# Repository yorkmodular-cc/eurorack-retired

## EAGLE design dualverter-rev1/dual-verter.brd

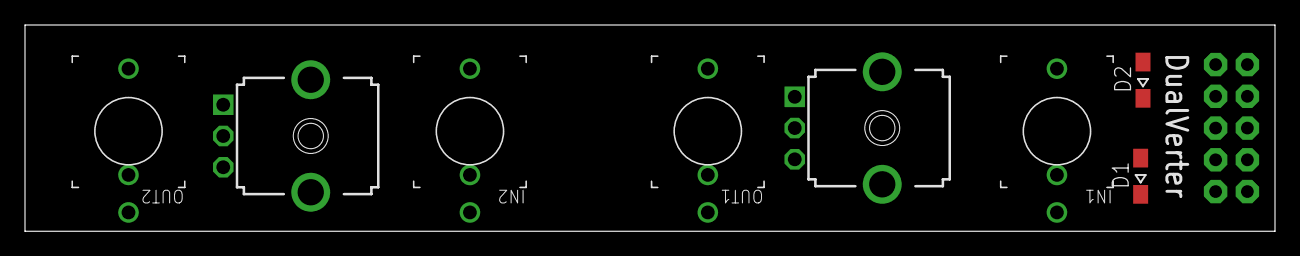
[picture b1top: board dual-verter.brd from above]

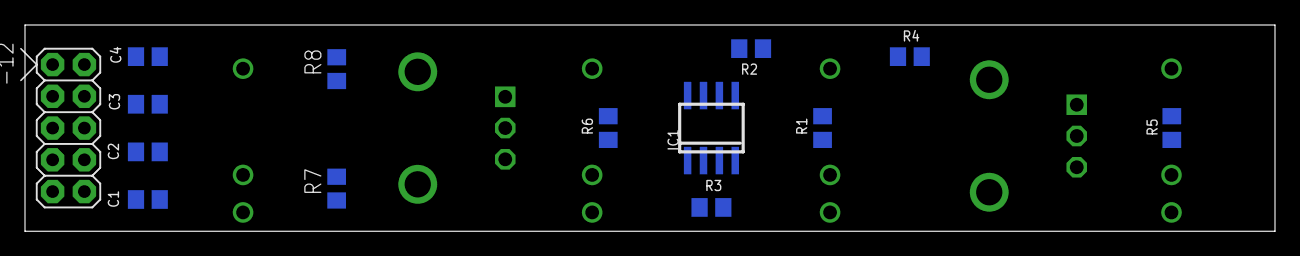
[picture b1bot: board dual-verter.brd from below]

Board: 2 copper layers, 100.0 x 16.5 mm, 22 parts (14 on the bottom side), 15 nets, no tracks yet.

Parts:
C1, C4: 10u; C0805
C2, C3: 0.1u; C0805
D1, D2: BAT54; SOD323-W
IC1: TL072D; SO08
IN1, IN2: THONKICONNNEW; WQP-PJ301M-12_JACK
OUT1, OUT2: THONKICONNNEW; WQP-PJ301M-12_JACK
POWER1: POWER_SIMPLE10; POWER_10
R1, R2, R3, R4, R5, R6: 200k; R0805
R7, R8: FERRITE; R0805
VR1, VR2: 100k; 9MM_SNAP-IN_POT

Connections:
+12V: C1.1, C2.1, D1.C, IC1.8, R7.2
-12V: C3.2, C4.2, D2.A, IC1.4, R8.1
GND: C1.2, C2.2, C3.1, C4.1, D1.A, D2.C, IN1.P$2_SWITCH, IN1.P$3_SLEEVE, IN2.P$3_SLEEVE, OUT1.P$2_SWITCH, OUT1.P$3_SLEEVE, OUT2.P$2_SWITCH, OUT2.P$3_SLEEVE, POWER1.3, POWER1.4, POWER1.5, POWER1.6, POWER1.7, POWER1.8, VR1.1, VR2.1
IN1: IN1.P$1_TIP, IN2.P$2_SWITCH, R1.1, VR1.3
unnamed: IC1.3, VR1.2
unnamed: IC1.5, VR2.2
unnamed: IC1.7, R4.2, R5.1
unnamed: IN2.P$1_TIP, R2.1, VR2.3
unnamed: IC1.1, R3.2, R6.1
unnamed: IC1.2, R1.2, R3.1
unnamed: POWER1.9, POWER1.10, R7.1
unnamed: IC1.6, R2.2, R4.1
unnamed: OUT2.P$1_TIP, R5.2
unnamed: OUT1.P$1_TIP, R6.2
unnamed: POWER1.1, POWER1.2, R8.2

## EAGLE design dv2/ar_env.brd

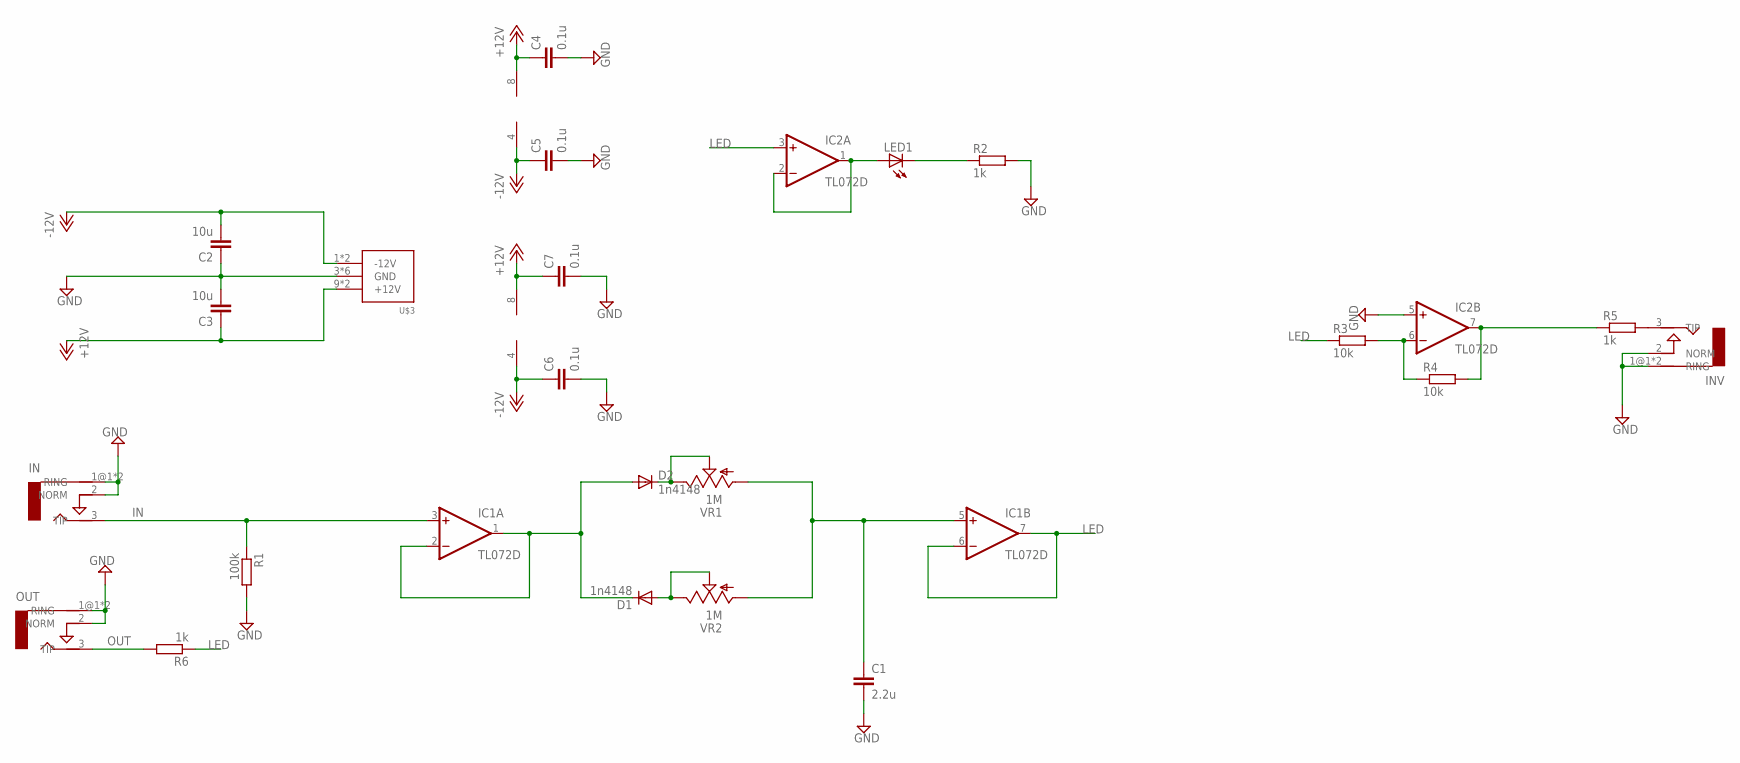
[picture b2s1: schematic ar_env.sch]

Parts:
C1: 2.2u; C0805
C2, C3: 10u; C0805
C4, C5, C6, C7: 0.1u; C0805
D1, D2: 1n4148; SOD323-W
IC1, IC2: TL072D; SO08
IN: AUDIO-JACKERTHENVAR; ERTHENVAR-JACK
INV: AUDIO-JACKERTHENVAR; ERTHENVAR-JACK
LED1: LEDCHIP-LED0805; CHIP-LED0805
OUT: AUDIO-JACKERTHENVAR; ERTHENVAR-JACK
R1: 100k; R0805
R2, R5, R6: 1k; R0805
R3, R4: 10k; R0805
U$3: POWER_SIMPLE10; POWER_10
VR1, VR2: 1M; 9MM_SNAP-IN_POT

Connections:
+12V: C3.1, C4.1, C7.1, IC1.8 (V+), IC2.8 (V+), U$3.9 (+12V), U$3.10 (+12V)
-12V: C2.2, C5.1, C6.1, IC1.4 (V-), IC2.4 (V-), U$3.1 (-12V), U$3.2 (-12V)
GND: C1.2, C2.1, C3.2, C4.2, C5.2, C6.2, C7.2, IC2.5 (+IN), IN.1@1 (RING), IN.1@2 (RING), IN.2 (NORM), INV.1@1 (RING), INV.1@2 (RING), INV.2 (NORM), OUT.1@1 (RING), OUT.1@2 (RING), OUT.2 (NORM), R1.2, R2.2, U$3.3 (GND), U$3.4 (GND), U$3.5 (GND), U$3.6 (GND), U$3.7 (GND), U$3.8 (GND)
IN: IC1.3 (+IN), IN.3 (TIP), R1.1
LED: IC1.6 (-IN), IC1.7 (OUT), IC2.3 (+IN), R3.1, R6.1
unnamed: D2.C, VR1.2 (S), VR1.3 (E)
unnamed: D1.A, VR2.2 (S), VR2.3 (E)
unnamed: D1.C, D2.A, IC1.1 (OUT), IC1.2 (-IN)
unnamed: IC2.1 (OUT), IC2.2 (-IN), LED1.A
unnamed: C1.1, IC1.5 (+IN), VR1.1 (A), VR2.1 (A)
unnamed: IC2.7 (OUT), R4.2, R5.1
unnamed: IC2.6 (-IN), R3.2, R4.1
unnamed: LED1.C, R2.1
unnamed: INV.3 (TIP), R5.2
OUT: OUT.3 (TIP), R6.2

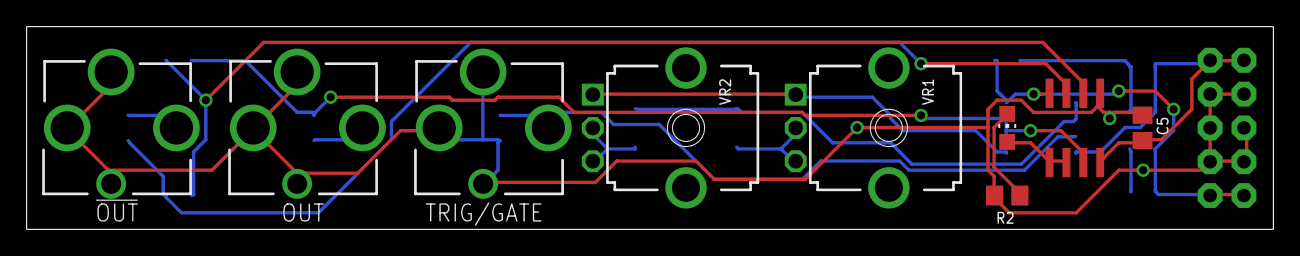
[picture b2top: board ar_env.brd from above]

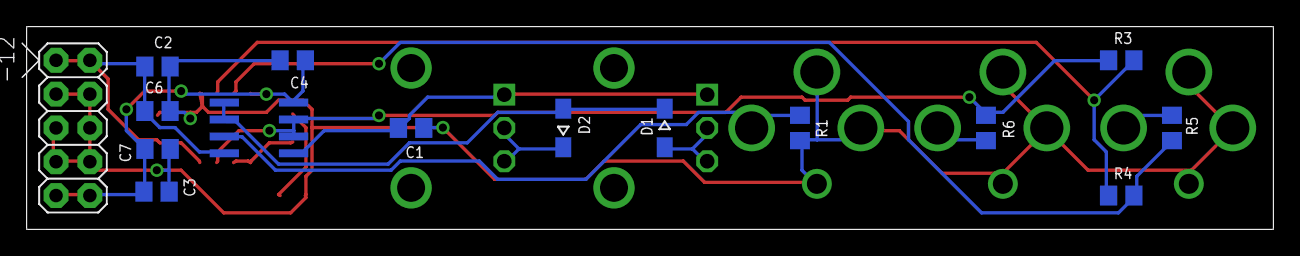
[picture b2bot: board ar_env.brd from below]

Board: 2 copper layers, 93.6 x 15.2 mm, 24 parts (15 on the bottom side), 15 nets.

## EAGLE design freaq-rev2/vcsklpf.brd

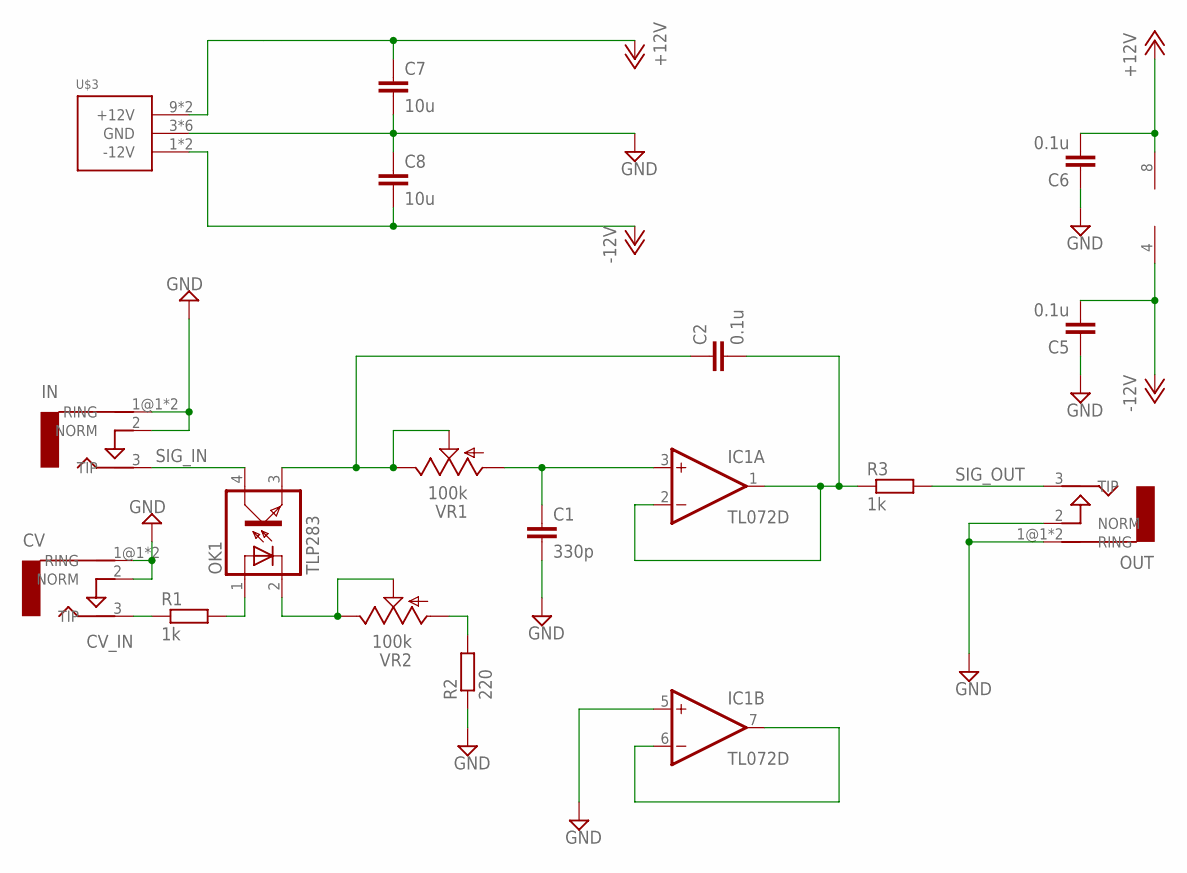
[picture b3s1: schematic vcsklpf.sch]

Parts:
C1: 330p; C0805
C2, C5, C6: 0.1u; C0805
C7, C8: 10u; C0805
CV: AUDIO-JACKERTHENVAR; ERTHENVAR-JACK
IC1: TL072D; SO08
IN: AUDIO-JACKERTHENVAR; ERTHENVAR-JACK
OK1: TLP283; MINI-FLAT-4
OUT: AUDIO-JACKERTHENVAR; ERTHENVAR-JACK
R1, R3: 1k; R0805
R2: 220; R0805
U$3: POWER_SIMPLE10; POWER_10
VR1, VR2: 100k; 9MM_SNAP-IN_POT

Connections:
+12V: C6.2, C7.1, IC1.8 (V+), U$3.9 (+12V), U$3.10 (+12V)
-12V: C5.2, C8.2, IC1.4 (V-), U$3.1 (-12V), U$3.2 (-12V)
CV_IN: CV.3 (TIP), R1.1
GND: C1.2, C5.1, C6.1, C7.2, C8.1, CV.1@1 (RING), CV.1@2 (RING), CV.2 (NORM), IC1.5 (+IN), IN.1@1 (RING), IN.1@2 (RING), IN.2 (NORM), OUT.1@1 (RING), OUT.1@2 (RING), OUT.2 (NORM), R2.1, U$3.3 (GND), U$3.4 (GND), U$3.5 (GND), U$3.6 (GND), U$3.7 (GND), U$3.8 (GND)
unnamed: C2.2, IC1.1 (OUT), IC1.2 (-IN), R3.1
unnamed: C1.1, IC1.3 (+IN), VR1.1 (A)
unnamed: C2.1, OK1.3 (EMIT), VR1.2 (S), VR1.3 (E)
unnamed: IC1.6 (-IN), IC1.7 (OUT)
unnamed: OK1.2 (C), VR2.2 (S), VR2.3 (E)
unnamed: OK1.1 (A), R1.2
unnamed: R2.2, VR2.1 (A)
SIG_IN: IN.3 (TIP), OK1.4 (COL)
SIG_OUT: OUT.3 (TIP), R3.2

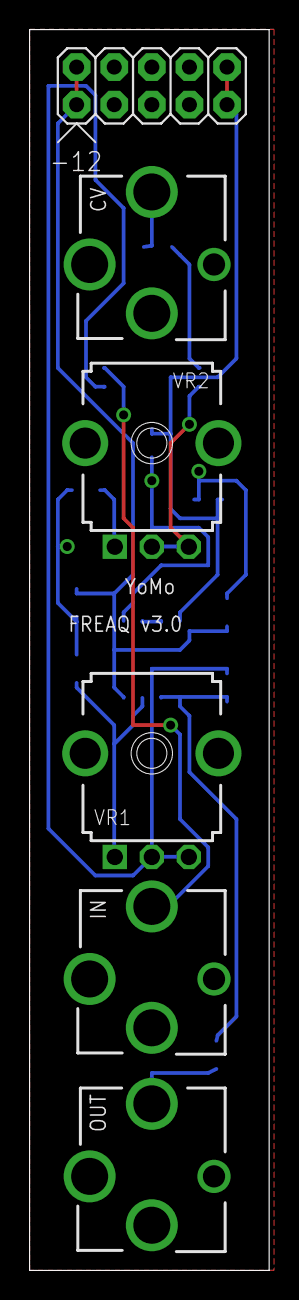
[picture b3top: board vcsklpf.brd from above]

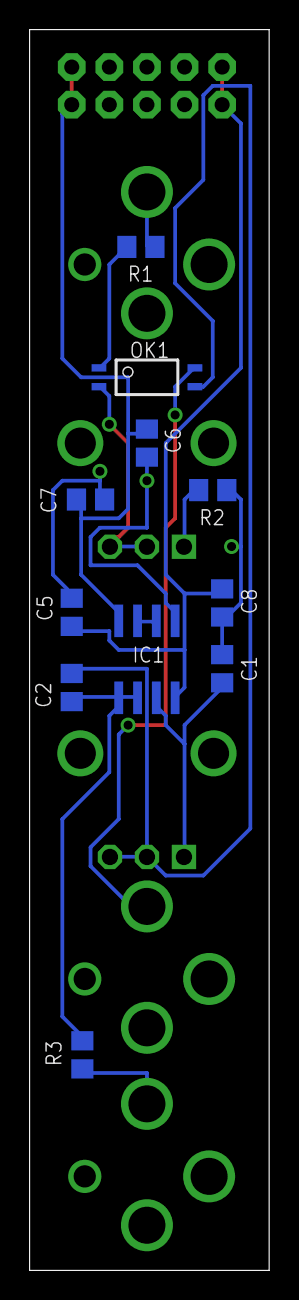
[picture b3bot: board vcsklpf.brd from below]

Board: 2 copper layers, 16.2 x 83.8 mm, 17 parts (11 on the bottom side), 13 nets.

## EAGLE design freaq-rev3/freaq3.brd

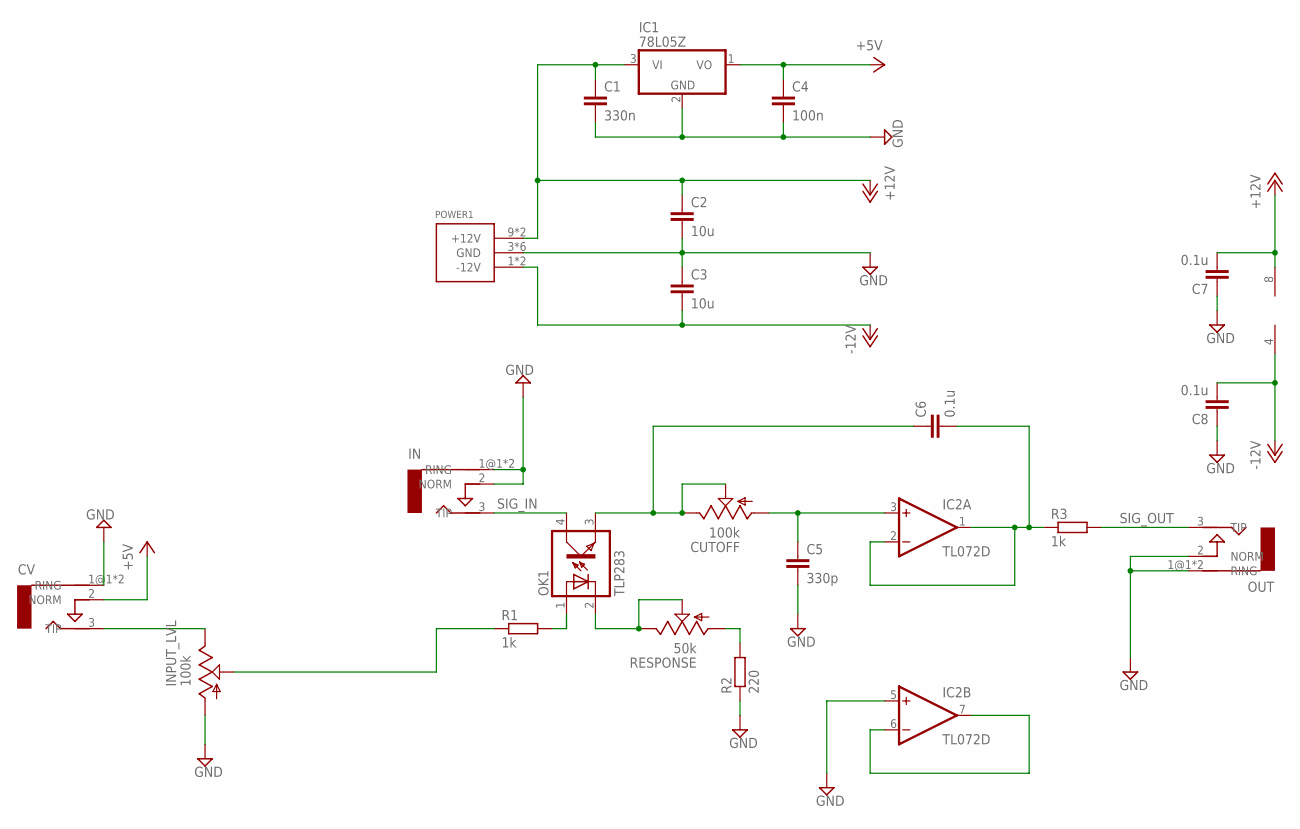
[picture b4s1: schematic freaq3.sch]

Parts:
C1: 330n; C0805
C2, C3: 10u; C0805
C4: 100n; C0805
C5: 330p; C0805
C6, C7, C8: 0.1u; C0805
CUTOFF: 100k; 9MM_SNAP-IN_POT
CV: AUDIO-JACKERTHENVAR; ERTHENVAR-JACK
IC1: 78L05Z; TO92
IC2: TL072D; SO08
IN: AUDIO-JACKERTHENVAR; ERTHENVAR-JACK
INPUT_LVL: 100k; 9MM_SNAP-IN_POT
OK1: TLP283; MINI-FLAT-4
OUT: AUDIO-JACKERTHENVAR; ERTHENVAR-JACK
POWER1: POWER_SIMPLE10; POWER_10
R1, R3: 1k; R0805
R2: 220; R0805
RESPONSE: 50k; 9MM_SNAP-IN_POT

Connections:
+5V: C4.1, CV.2 (NORM), IC1.1 (VO)
+12V: C1.1, C2.1, C7.2, IC1.3 (VI), IC2.8 (V+), POWER1.9 (+12V), POWER1.10 (+12V)
-12V: C3.2, C8.2, IC2.4 (V-), POWER1.1 (-12V), POWER1.2 (-12V)
GND: C1.2, C2.2, C3.1, C4.2, C5.2, C7.1, C8.1, CV.1@1 (RING), CV.1@2 (RING), IC1.2 (GND), IC2.5 (+IN), IN.1@1 (RING), IN.1@2 (RING), IN.2 (NORM), INPUT_LVL.1 (A), OUT.1@1 (RING), OUT.1@2 (RING), OUT.2 (NORM), POWER1.3 (GND), POWER1.4 (GND), POWER1.5 (GND), POWER1.6 (GND), POWER1.7 (GND), POWER1.8 (GND), R2.1
unnamed: C6.2, IC2.1 (OUT), IC2.2 (-IN), R3.1
unnamed: C5.1, CUTOFF.1 (A), IC2.3 (+IN)
unnamed: C6.1, CUTOFF.2 (S), CUTOFF.3 (E), OK1.3 (EMIT)
unnamed: INPUT_LVL.2 (S), R1.1
unnamed: IC2.6 (-IN), IC2.7 (OUT)
unnamed: CV.3 (TIP), INPUT_LVL.3 (E)
unnamed: OK1.2 (C), RESPONSE.2 (S), RESPONSE.3 (E)
unnamed: OK1.1 (A), R1.2
unnamed: R2.2, RESPONSE.1 (A)
SIG_IN: IN.3 (TIP), OK1.4 (COL)
SIG_OUT: OUT.3 (TIP), R3.2

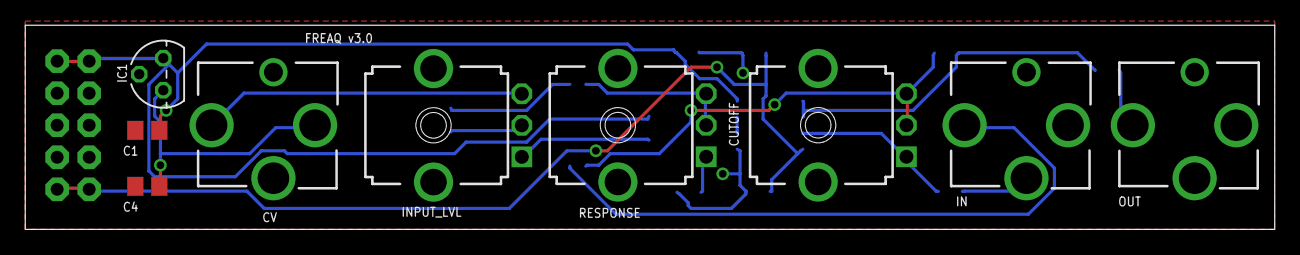
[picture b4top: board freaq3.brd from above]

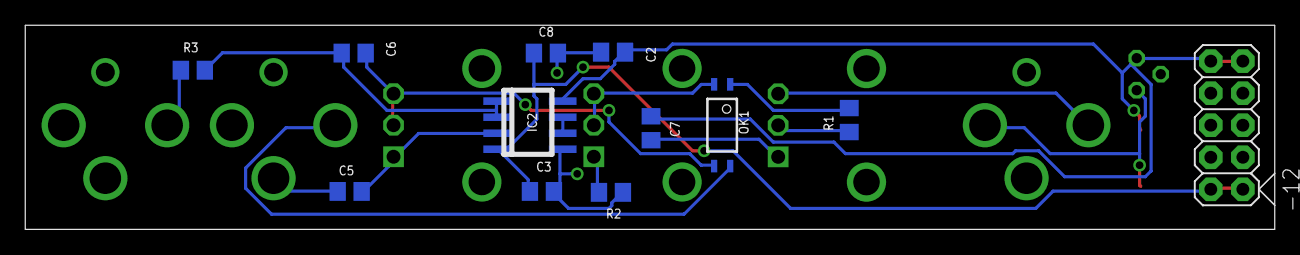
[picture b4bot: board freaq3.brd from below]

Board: 2 copper layers, 99.1 x 16.2 mm, 21 parts (12 on the bottom side), 15 nets.

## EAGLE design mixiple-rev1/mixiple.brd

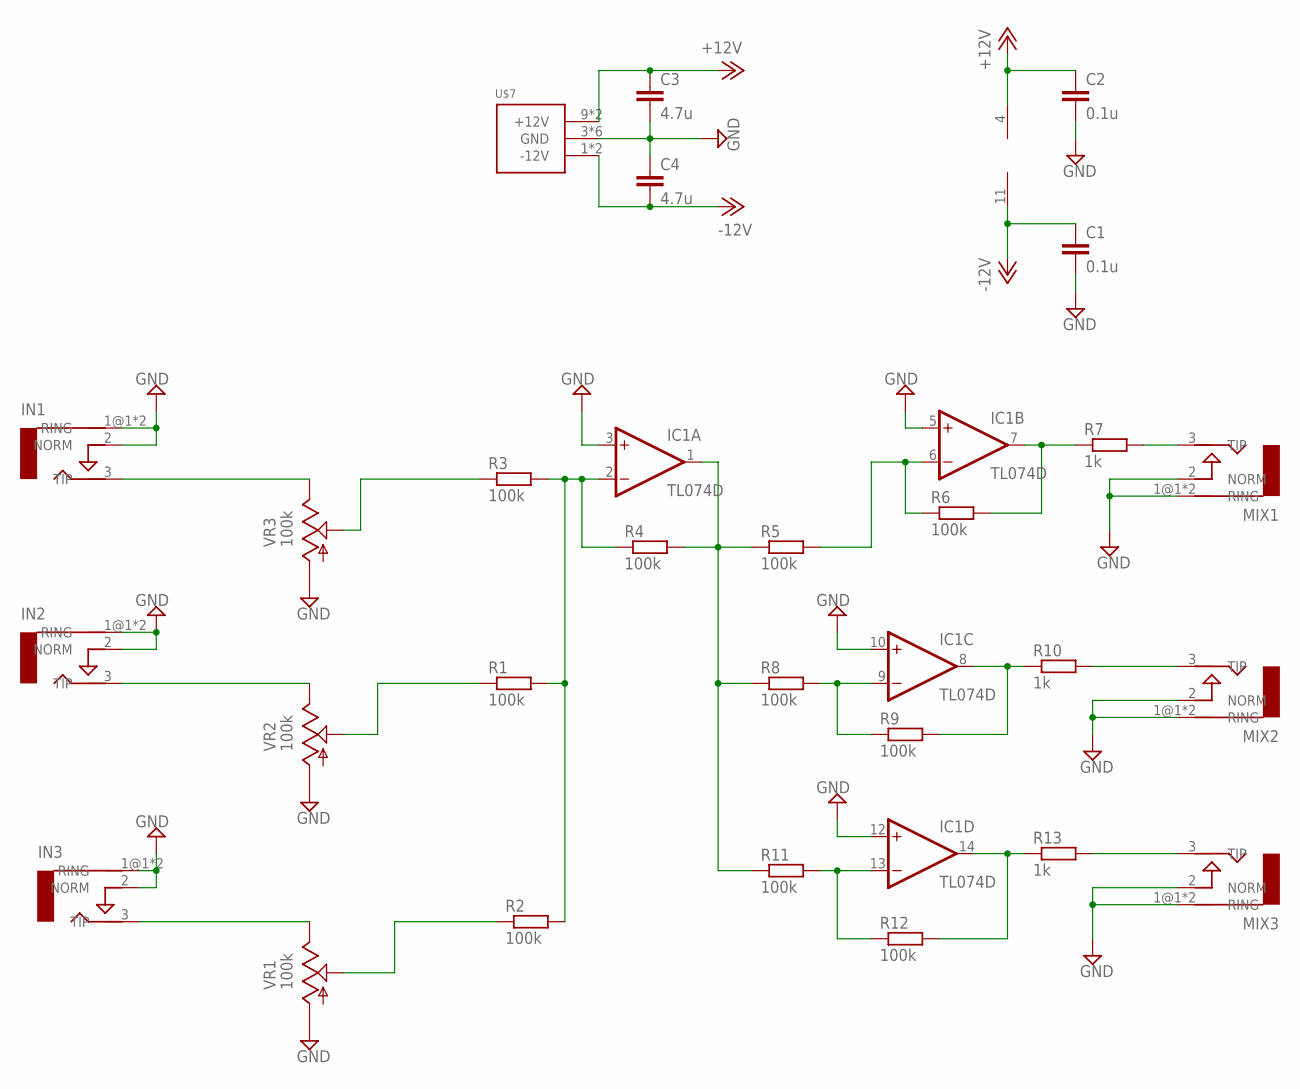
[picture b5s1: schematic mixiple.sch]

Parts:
C1, C2: 0.1u; C0805
C3, C4: 4.7u; C0805
IC1: TL074D; SO14
IN1, IN2, IN3: AUDIO-JACKERTHENVAR; ERTHENVAR-JACK
MIX1, MIX2, MIX3: AUDIO-JACKERTHENVAR; ERTHENVAR-JACK
R1, R2, R3, R4, R5, R6, R8, R9, R11, R12: 100k; R0805
R7, R10, R13: 1k; R0805
U$7: POWER_SIMPLE10; POWER_10
VR1, VR2, VR3: 100k; 9MM_SNAP-IN_POT

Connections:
+12V: C2.1, C3.1, IC1.4 (V+), U$7.9 (+12V), U$7.10 (+12V)
-12V: C1.1, C4.2, IC1.11 (V-), U$7.1 (-12V), U$7.2 (-12V)
GND: C1.2, C2.2, C3.2, C4.1, IC1.3 (+IN), IC1.5 (+IN), IC1.10 (+IN), IC1.12 (+IN), IN1.1@1 (RING), IN1.1@2 (RING), IN1.2 (NORM), IN2.1@1 (RING), IN2.1@2 (RING), IN2.2 (NORM), IN3.1@1 (RING), IN3.1@2 (RING), IN3.2 (NORM), MIX1.1@1 (RING), MIX1.1@2 (RING), MIX1.2 (NORM), MIX2.1@1 (RING), MIX2.1@2 (RING), MIX2.2 (NORM), MIX3.1@1 (RING), MIX3.1@2 (RING), MIX3.2 (NORM), U$7.3 (GND), U$7.4 (GND), U$7.5 (GND), U$7.6 (GND), U$7.7 (GND), U$7.8 (GND), VR1.1 (A), VR2.1 (A), VR3.1 (A)
unnamed: R2.1, VR1.2 (S)
unnamed: R1.1, VR2.2 (S)
unnamed: R3.1, VR3.2 (S)
unnamed: IC1.7 (OUT), R6.2, R7.1
unnamed: IC1.8 (OUT), R9.2, R10.1
unnamed: IC1.14 (OUT), R12.2, R13.1
unnamed: IC1.6 (-IN), R5.2, R6.1
unnamed: IC1.9 (-IN), R8.2, R9.1
unnamed: IC1.13 (-IN), R11.2, R12.1
unnamed: IN1.3 (TIP), VR3.3 (E)
unnamed: IC1.2 (-IN), R1.2, R2.2, R3.2, R4.1
unnamed: IN2.3 (TIP), VR2.3 (E)
unnamed: IN3.3 (TIP), VR1.3 (E)
unnamed: IC1.1 (OUT), R4.2, R5.1, R8.1, R11.1
unnamed: MIX2.3 (TIP), R10.2
unnamed: MIX3.3 (TIP), R13.2
unnamed: MIX1.3 (TIP), R7.2

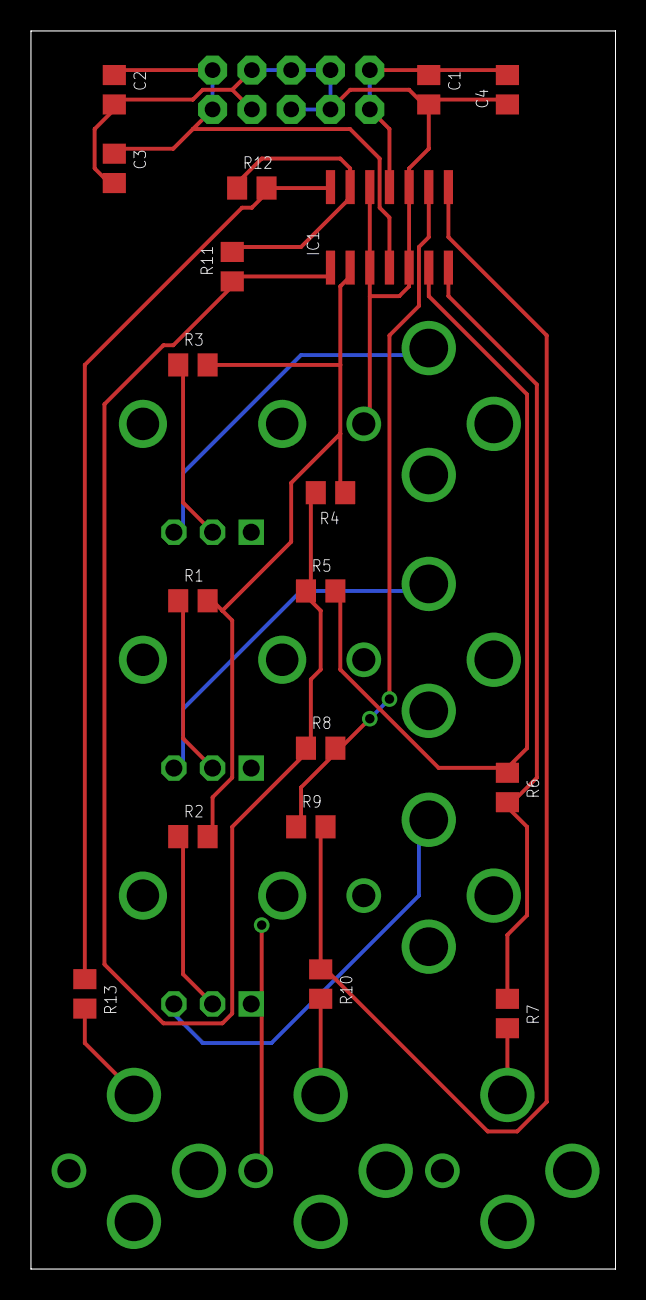
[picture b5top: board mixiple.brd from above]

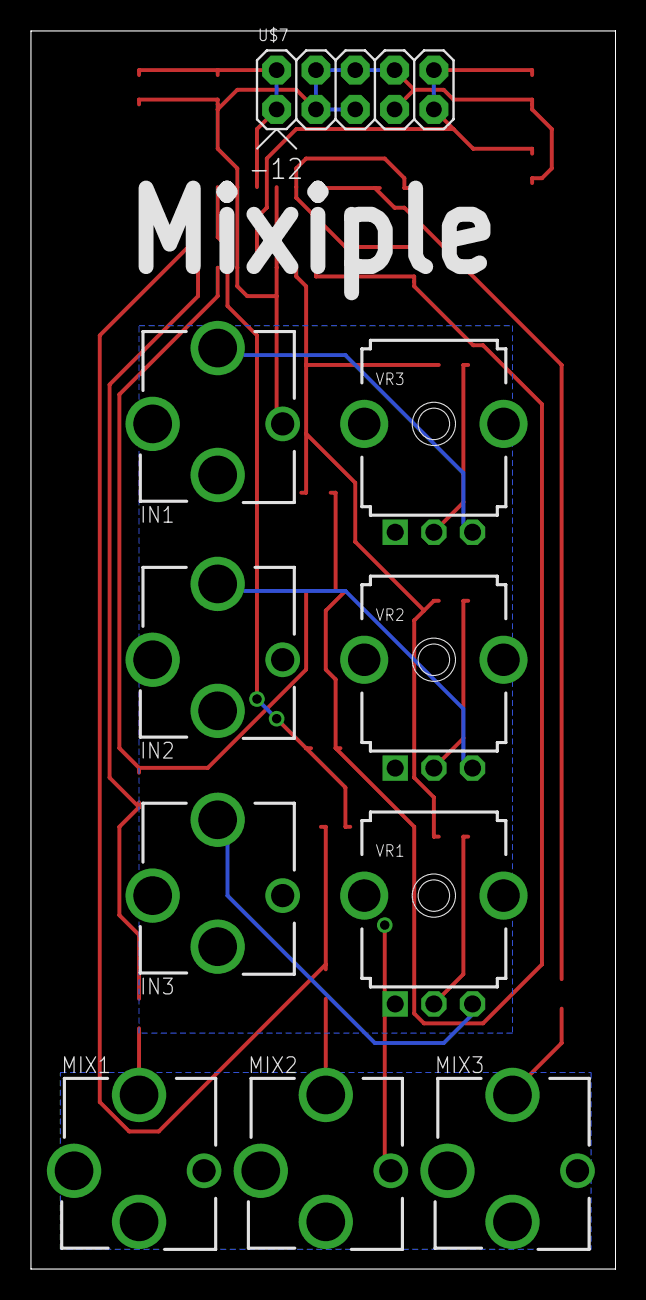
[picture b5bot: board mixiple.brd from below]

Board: 2 copper layers, 37.8 x 80.0 mm, 28 parts (10 on the bottom side), 20 nets.

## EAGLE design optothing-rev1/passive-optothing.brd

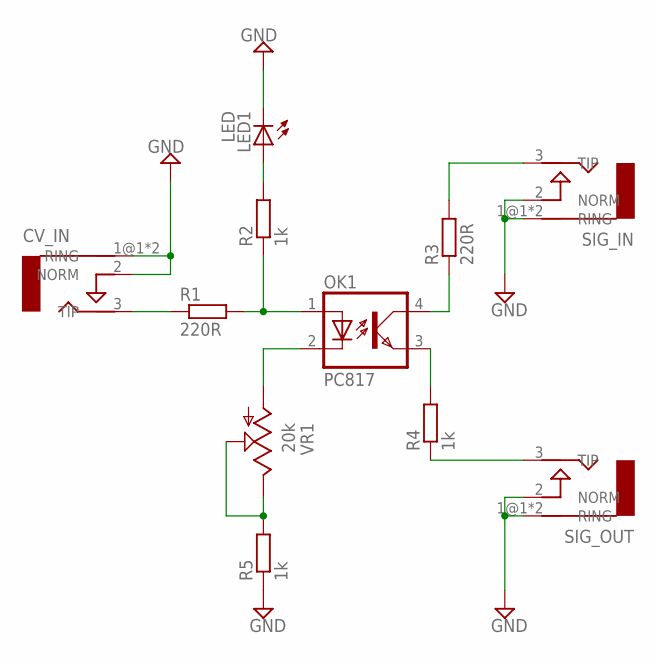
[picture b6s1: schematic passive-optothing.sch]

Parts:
CV_IN: AUDIO-JACKERTHENVAR; ERTHENVAR-JACK
LED1: LED; LED3MM
OK1: PC817; DIL04
R1, R3: 220R; R0805
R2, R4, R5: 1k; R0805
SIG_IN: AUDIO-JACKERTHENVAR; ERTHENVAR-JACK
SIG_OUT: AUDIO-JACKERTHENVAR; ERTHENVAR-JACK
VR1: 20k; 9MM_SNAP-IN_POT

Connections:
CV_IN: OK1.1 (A), R1.2, R2.1
CV_OUT: OK1.2 (C), VR1.1 (A)
GND: CV_IN.1@1 (RING), CV_IN.1@2 (RING), CV_IN.2 (NORM), LED1.K (C), R5.1, SIG_IN.1@1 (RING), SIG_IN.1@2 (RING), SIG_IN.2 (NORM), SIG_OUT.1@1 (RING), SIG_OUT.1@2 (RING), SIG_OUT.2 (NORM)
unnamed: R5.2, VR1.2 (S), VR1.3 (E)
unnamed: R4.1, SIG_OUT.3 (TIP)
unnamed: OK1.4 (COL), R3.1
unnamed: CV_IN.3 (TIP), R1.1
unnamed: LED1.A, R2.2
SIG_IN: R3.2, SIG_IN.3 (TIP)
SIG_OUT: OK1.3 (EMIT), R4.2

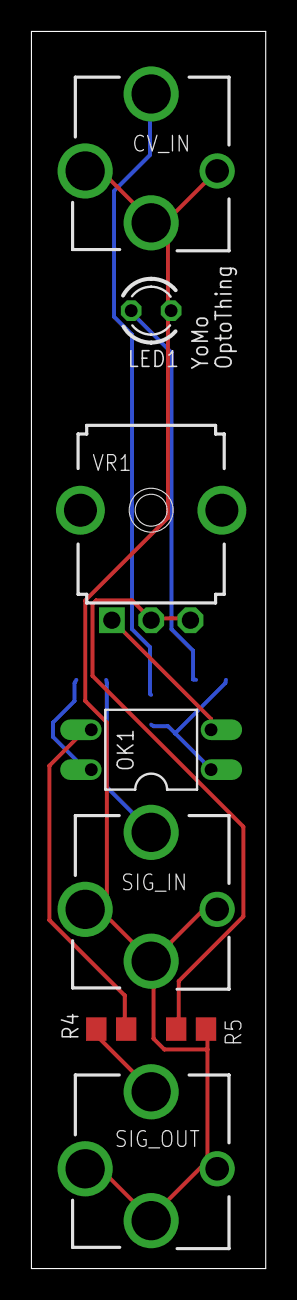
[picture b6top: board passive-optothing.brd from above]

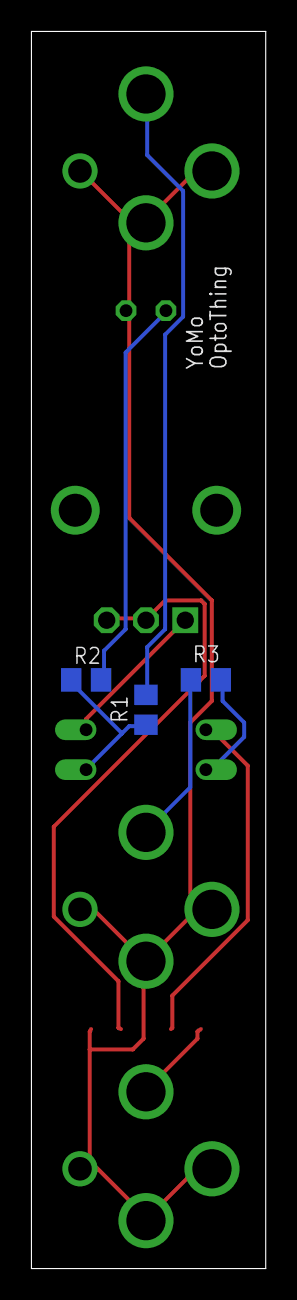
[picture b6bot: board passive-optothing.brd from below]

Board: 2 copper layers, 14.9 x 78.7 mm, 11 parts (3 on the bottom side), 10 nets.

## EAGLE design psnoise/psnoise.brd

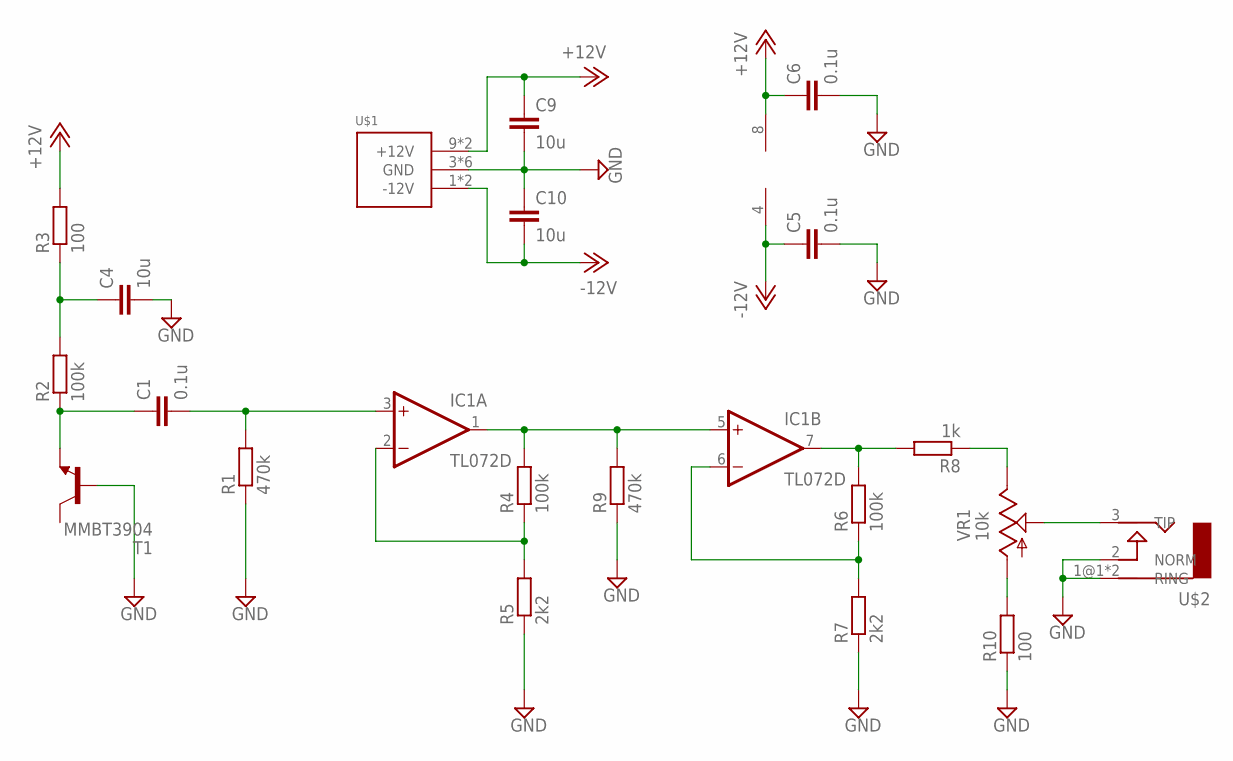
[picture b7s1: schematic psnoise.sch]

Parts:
C1, C5, C6: 0.1u; C0805
C4, C9, C10: 10u; C0805
IC1: TL072D; SO08
R1, R9: 470k; R0805
R2, R4, R6: 100k; R0805
R3, R10: 100; R0805
R5, R7: 2k2; R0805
R8: 1k; R0805
T1: MMBT3904; SOT23-BEC
U$1: POWER_SIMPLE10; POWER_10
U$2: AUDIO-JACKERTHENVAR; ERTHENVAR-JACK
VR1: 10k; 9MM_SNAP-IN_POT

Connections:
+12V: C6.1, C9.1, IC1.8 (V+), R3.2, U$1.9 (+12V), U$1.10 (+12V)
-12V: C5.1, C10.2, IC1.4 (V-), U$1.1 (-12V), U$1.2 (-12V)
GND: C4.2, C5.2, C6.2, C9.2, C10.1, R1.1, R5.1, R7.1, R9.1, R10.1, T1.B, U$1.3 (GND), U$1.4 (GND), U$1.5 (GND), U$1.6 (GND), U$1.7 (GND), U$1.8 (GND), U$2.1@1 (RING), U$2.1@2 (RING), U$2.2 (NORM)
unnamed: IC1.2 (-IN), R4.1, R5.2
unnamed: IC1.1 (OUT), IC1.5 (+IN), R4.2, R9.2
unnamed: R10.2, VR1.1 (A)
unnamed: IC1.6 (-IN), R6.1, R7.2
unnamed: IC1.7 (OUT), R6.2, R8.2
unnamed: R8.1, VR1.3 (E)
unnamed: C1.2, IC1.3 (+IN), R1.2
unnamed: U$2.3 (TIP), VR1.2 (S)
unnamed: C4.1, R2.2, R3.1
unnamed: C1.1, R2.1, T1.E

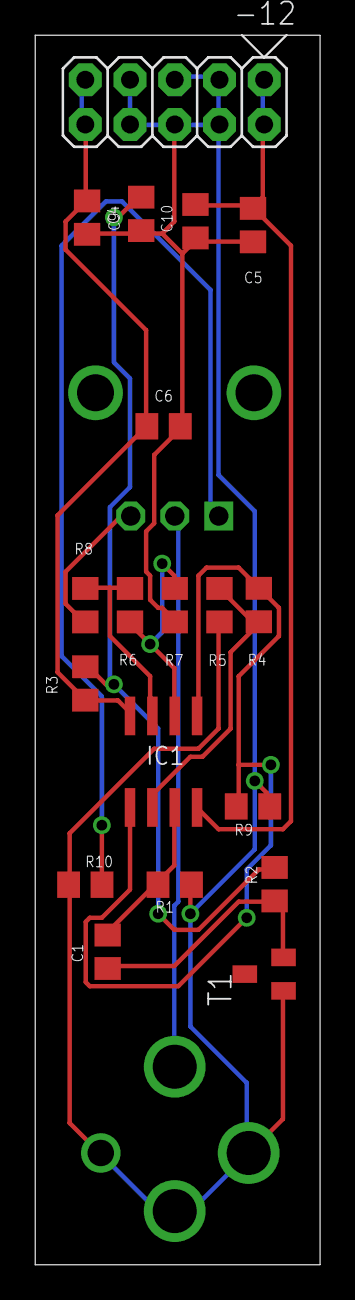
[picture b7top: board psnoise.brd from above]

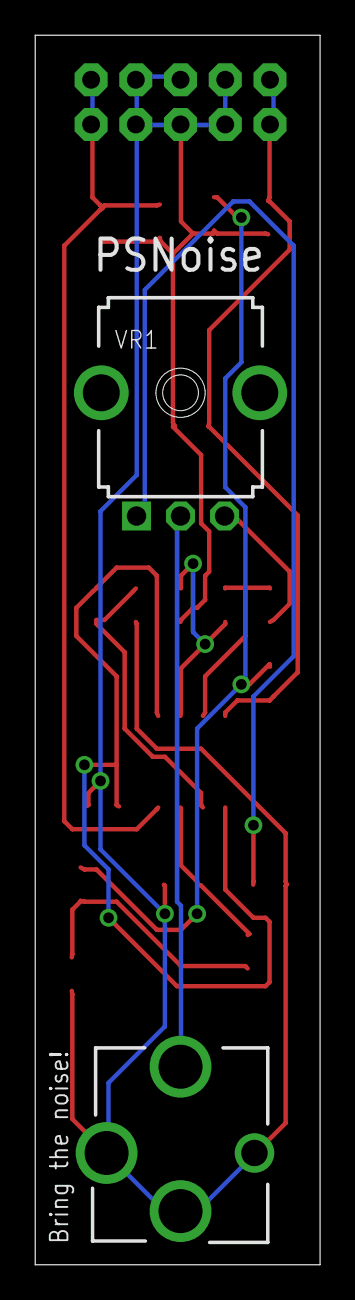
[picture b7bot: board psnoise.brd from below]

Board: 2 copper layers, 16.2 x 69.8 mm, 21 parts (2 on the bottom side), 13 nets.
